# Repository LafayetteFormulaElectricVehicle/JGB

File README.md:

# LFEV 2015 CAN Communications Microprocessor #

## For now we have decided not to add JGBs to the system
JGBs provide good developement platforms but we will use the hardware and software in special configurations in each subsystem.

This directory contains the Lafayette College Formula Electric Vehicle CAN Communications Board. This board is responsible for relaying all low level inputs and outputs (ADC, D2A, GPIO) from vehicle sub-systems to the main SCADA computer. This design contains both hardware (PCB), and the firmware written for the device.

## Hardware ##
All hardware was created in KiCad (old-stable), and is located in the 'hardware' directory. The project is described in more detail there.

## Software ##
Software written for this project is located in the 'software' directory. The target architecture for the firmware is the ATMega16M1 AVR. Software build proceedures, programming the device, and project organization are all described in more detail in the folder.

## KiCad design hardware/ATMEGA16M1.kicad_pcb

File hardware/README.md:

# LFEV 2015 CAN Communications Microprocessor Hardware #
This directory contains the CAN communications board (JGB) designed for the spring 2015 semester.

## Overview ##
This circuit board is the primary interface between SCADA and all other systems. It is used to interface low level devices such as relays, ADCs, and other inputs/outputs to the SCADA computer via a CAN bus. This board was designed for prototyping purposes, and ensures consitant message format is used on the CAN bus. Any device which communicates via the CAN bus should inteface through this board.

The microcontroller present on this board, and the software which runs on it should eventually be integrated into each node which must communicate via the CAN bus.

## System Capabilities ##

## Target Device ##
This software is written for the **Atmel ATMEGA 16M1 Automotive AVR**  
  
This device was selected for its price, software availability, documentation and onboard CAN bus support.

1. [ATMega16M1 Overview](http://www.atmel.com/devices/atmega16m1.aspx)
2. [ATMega16M1 Datasheet](http://www.atmel.com/images/doc8209.pdf)

### Features ###

* Atmel® AVR® 8-bit microcontroller
* Up to 1 MIPS throughput per MHz
* 16KBytes flash of in-system programmable program memory
* 512B of in-system programmable EEPROM
* 1KBytes internal SRAM
* On-chip debug interface (debugWIRE)
* CAN 2.0A/B with six message objects - ISO 16845 certified
* Variable PWM duty cycle and frequency
* Synchronous update of all PWM registers
* Peripheral features
* One 8-bit general purpose timer/counter
* One 16-bit general purpose timer/counter
* One master/slave SPI serial interface
* 10-bit ADC
	* 11 single ended channels
	* Three differential ADC channel pairs (5×, 10×, 20×, 40×)
* 10-bit DAC for variable voltage reference (comparators, ADC)
* Programmable watchdog timer with separate on-chip oscillator
* On-chip temperature sensor

### Operating Specifications ###

- Operating voltage: 2.7V - 5.5V
- Extended operating temperature:
- -40°C to +85°C
- Core speed grade:
- 0 - 8MHz @ 2.7 - 4.5V
- 0 - 16MHz @ 4.5 - 5.5V

## EDA Software Suite ##

### EDA Software Suite: ###
KiCad 'old-stable' was used to design this PCB. The technical revision was KiCad (2013-may-18)-stable, run under Gentoo Linux. The source code can be found at [kicad-20130518.ebuild](https://packages.gentoo.org/package/sci-electronics/kicad)

### Component Libraries: ###
The following KiCad libraries were used in the creation of this PCB.

1. [Walter KiCad Libraries](http://smisioto.no-ip.org/elettronica/kicad/kicad-en.htm)

### Gerber Files ###
The latest GERBER files submitted for fabrication can be found in the repository under 'can-embd/hardware/gerber/' or in the BitBucket 'Downloads' page.

## Bill of Materials ##
All parts for this board were ordered through digikey, and have a DigiKey parts number (P/N) and URL associated with them in the KiCad schematic.  
  
These associations can also be viewed in the Bill of Materials (hardware/BOM.csv).  
A BOM (DigiKey ID: 2503580) has been created, which is summarized in the 'DigiKey BOM' file below. 

1. [DigiKey BOM](DigiKey_BOM.csv) This BOM contains the required DigiKey parts to build a single board.
2. [KiCad BOM](BOM.csv) This file contains a list of all components generated by KiCad.

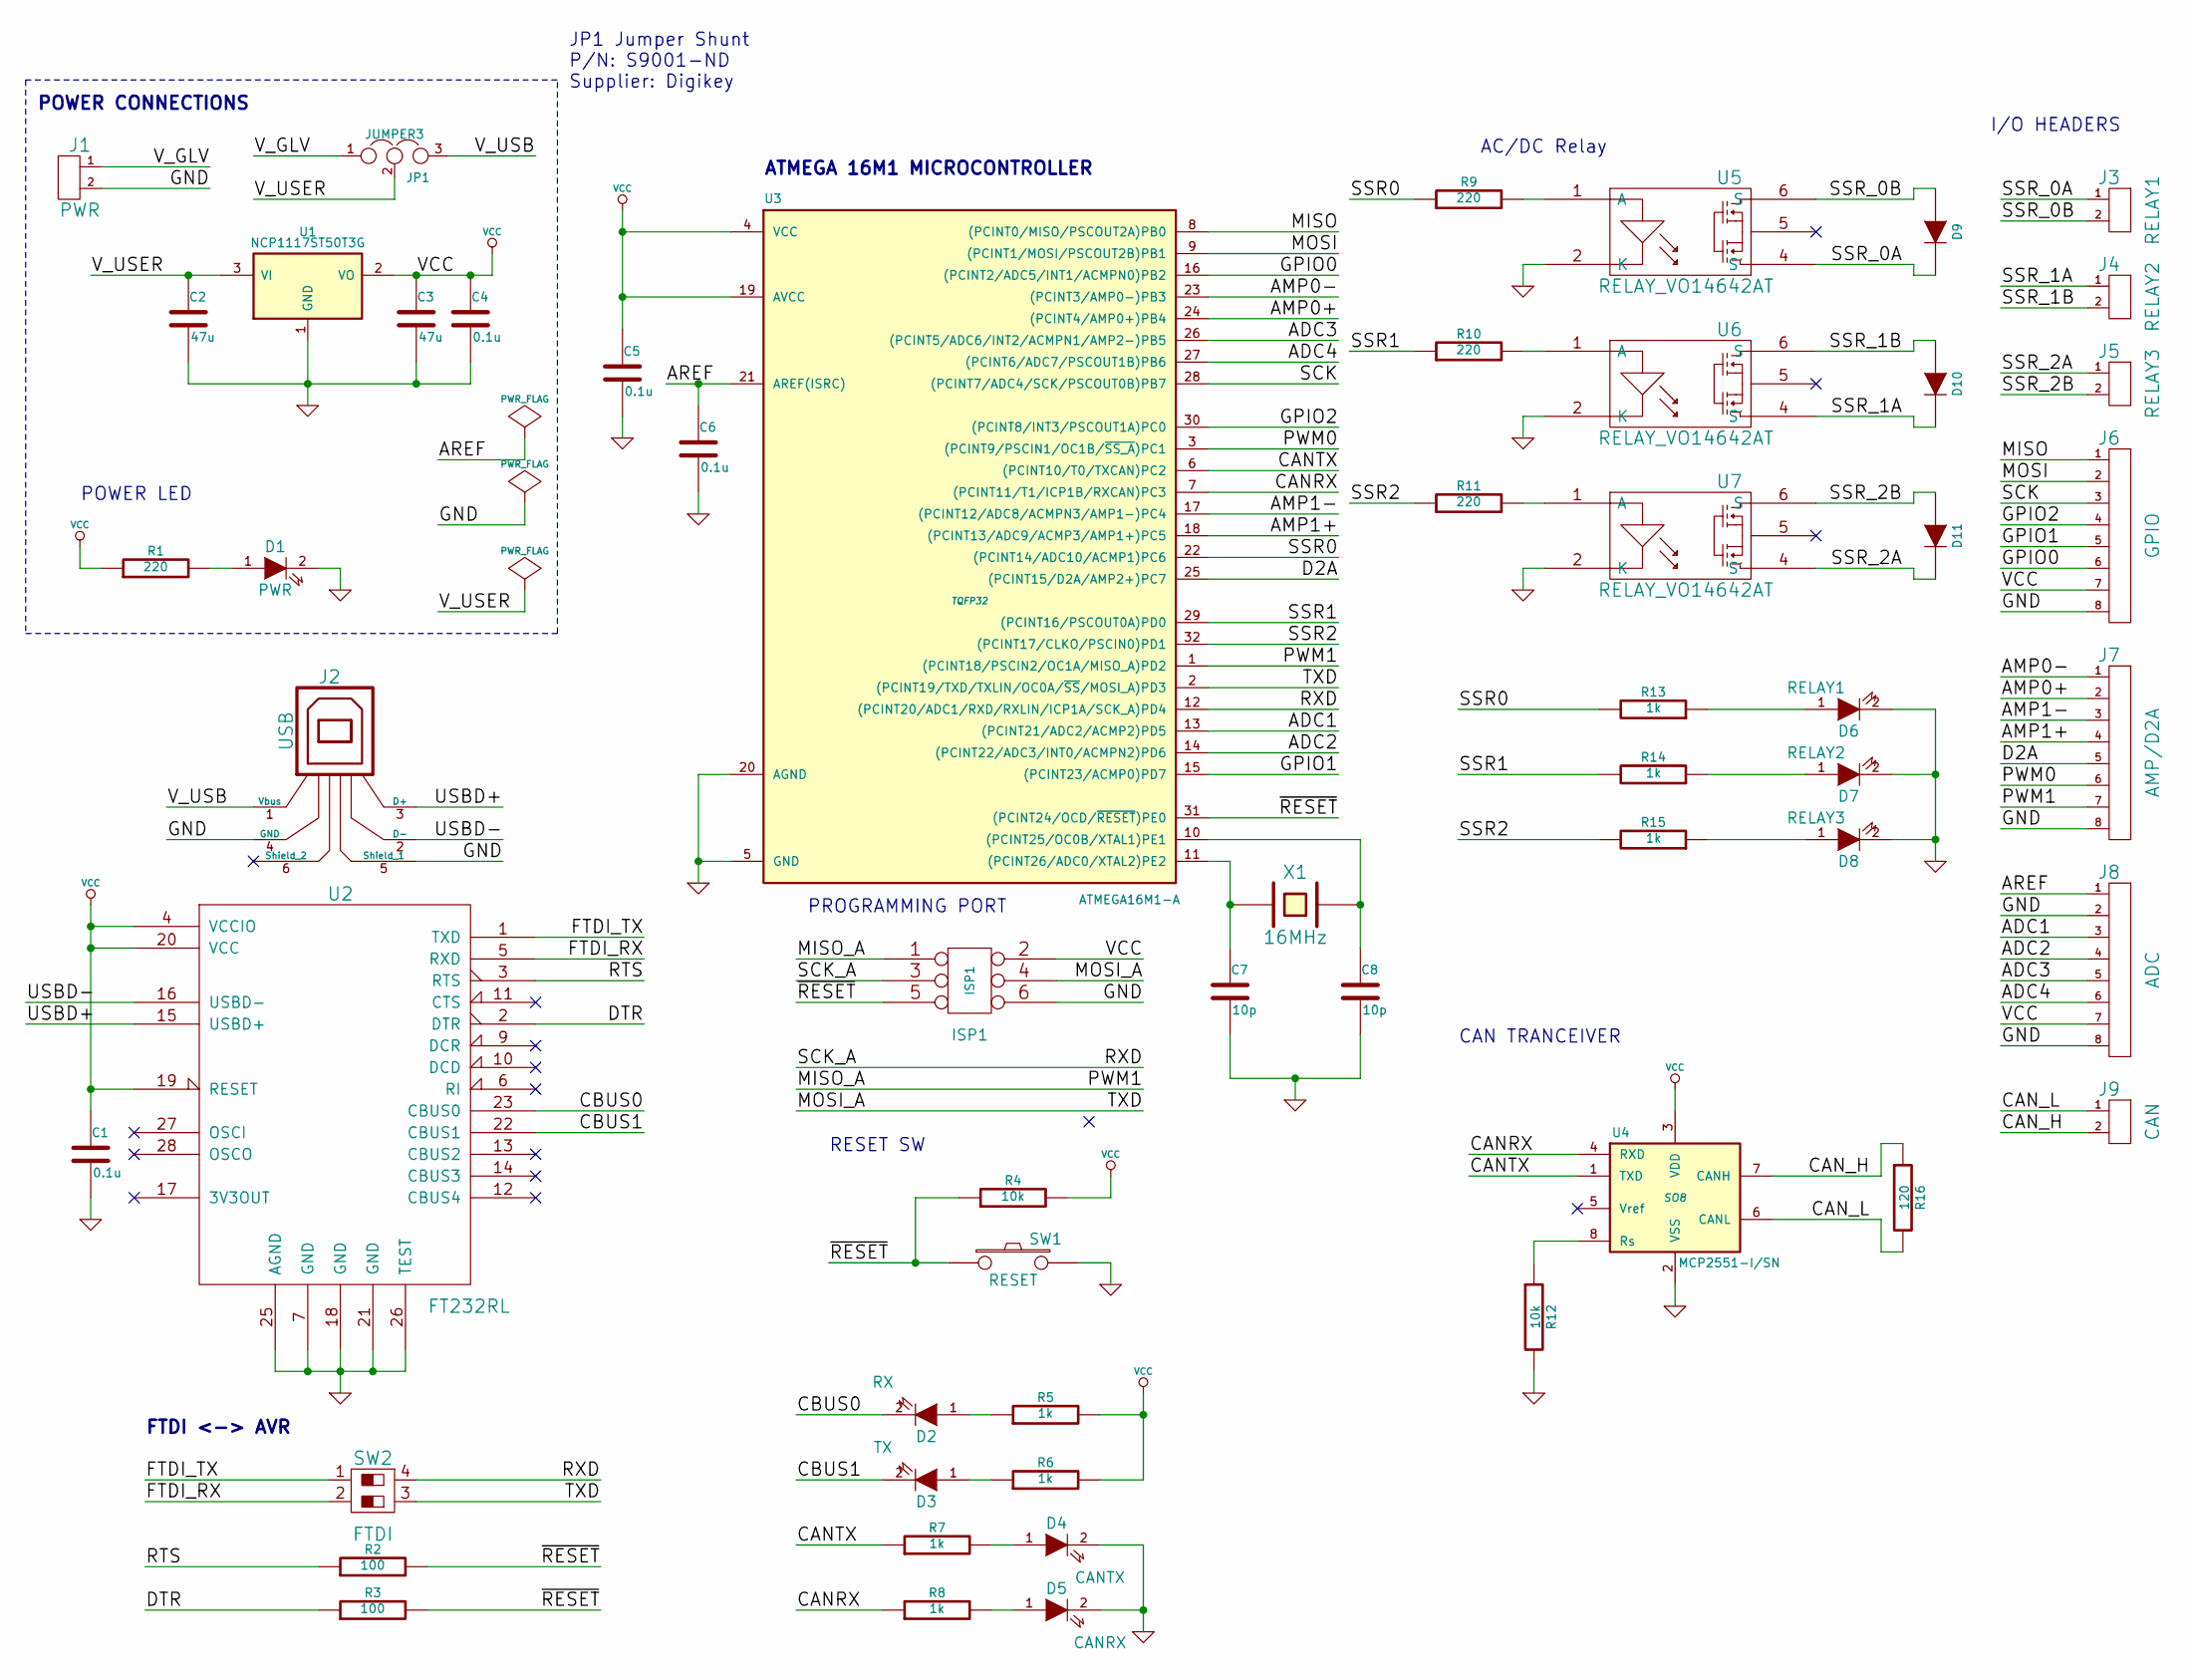
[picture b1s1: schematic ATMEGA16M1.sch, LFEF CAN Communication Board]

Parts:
C1, C4, C5, C6: 0.1u
C2, C3: 47u
C7, C8: 10p
D1: PWR
D2: RX
D3: TX
D4: CANTX
D5: CANRX
D6: RELAY1
D7: RELAY2
D8: RELAY3
D9, D10, D11: DIODE
ISP1: ISP1
J1: PWR
J2: USB
J3: RELAY1
J4: RELAY2
J5: RELAY3
J6: GPIO
J7: AMP/D2A
J8: ADC
J9: CAN
JP1: JUMPER3
R1, R9, R10, R11: 220
R2, R3: 100
R4, R12: 10k
R5, R6, R7, R8, R13, R14, R15: 1k
R16: 120
SW1: RESET
SW2: FTDI
U1: NCP1117ST50T3G
U2: FT232RL
U3: ATMEGA16M1-A; TQFP32
U4: MCP2551-I/SN; SO8
U5, U6, U7: RELAY_VO14642AT
X1: 16MHz

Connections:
/ADC1: J8.3, U3.13 ((PCINT21/ADC2/ACMP2)PD5)
/ADC2: J8.4, U3.14 ((PCINT22/ADC3/INT0/ACMPN2)PD6)
/ADC3: J8.5, U3.26 ((PCINT5/ADC6/INT2/ACMPN1/AMP2-)PB5)
/ADC4: J8.6, U3.27 ((PCINT6/ADC7/PSCOUT1B)PB6)
/AMP0+: J7.2, U3.24 ((PCINT4/AMP0+)PB4)
/AMP0-: J7.1, U3.23 ((PCINT3/AMP0-)PB3)
/AMP1+: J7.4, U3.18 ((PCINT13/ADC9/ACMP3/AMP1+)PC5)
/AMP1-: J7.3, U3.17 ((PCINT12/ADC8/ACMPN3/AMP1-)PC4)
/AREF: C6.1, J8.1, U3.21 (AREF(ISRC))
/CANRX: R8.1, U3.7 ((PCINT11/T1/ICP1B/RXCAN)PC3), U4.4 (RXD)
/CANTX: R7.1, U3.6 ((PCINT10/T0/TXCAN)PC2), U4.1 (TXD)
/CAN_H: J9.2, R16.1, U4.7 (CANH)
/CAN_L: J9.1, R16.2, U4.6 (CANL)
/CBUS0: D2.2 (K), U2.23 (CBUS0)
/CBUS1: D3.2 (K), U2.22 (CBUS1)
/D2A: J7.5, U3.25 ((PCINT15/D2A/AMP2+)PC7)
/DTR: R3.1, U2.2 (DTR)
/FTDI_RX: SW2.2, U2.5 (RXD)
/FTDI_TX: SW2.1, U2.1 (TXD)
/GPIO0: J6.6, U3.16 ((PCINT2/ADC5/INT1/ACMPN0)PB2)
/GPIO1: J6.5, U3.15 ((PCINT23/ACMP0)PD7)
/GPIO2: J6.4, U3.30 ((PCINT8/INT3/PSCOUT1A)PC0)
/MISO: J6.1, U3.8 ((PCINT0/MISO/PSCOUT2A)PB0)
/MISO_A: ISP1.1, J7.7, U3.1 ((PCINT18/PSCIN2/OC1A/MISO_A)PD2)
/MOSI: J6.2, U3.9 ((PCINT1/MOSI/PSCOUT2B)PB1)
/MOSI_A: ISP1.4, SW2.3, U3.2 ((PCINT19/TXD/TXLIN/OC0A/~SS~/MOSI_A)PD3)
/PWM0: J7.6, U3.3 ((PCINT9/PSCIN1/OC1B/~SS_A~)PC1)
/RTS: R2.1, U2.3 (RTS)
/RXD: ISP1.3, SW2.4, U3.12 ((PCINT20/ADC1/RXD/RXLIN/ICP1A/SCK_A)PD4)
/SCK: J6.3, U3.28 ((PCINT7/ADC4/SCK/PSCOUT0B)PB7)
/SSR0: R9.1, R13.2, U3.22 ((PCINT14/ADC10/ACMP1)PC6)
/SSR1: R10.1, R14.2, U3.29 ((PCINT16/PSCOUT0A)PD0)
/SSR2: R11.1, R15.2, U3.32 ((PCINT17/CLKO/PSCIN0)PD1)
/SSR_0A: D9.2 (K), J3.1, U5.4 (S')
/SSR_0B: D9.1 (A), J3.2, U5.6 (S)
/SSR_1A: D10.2 (K), J4.1, U6.4 (S')
/SSR_1B: D10.1 (A), J4.2, U6.6 (S)
/SSR_2A: D11.2 (K), J5.1, U7.4 (S')
/SSR_2B: D11.1 (A), J5.2, U7.6 (S)
/USBD+: J2.3 (D+), U2.15 (USBD+)
/USBD-: J2.2 (D-), U2.16 (USBD-)
/V_GLV: J1.1, JP1.1
/V_USB: J2.1 (Vbus), JP1.3
/V_USER: C2.1, JP1.2, U1.3 (VI)
/~RESET: ISP1.5, R2.2, R3.2, R4.1, SW1.1, U3.31 ((PCINT24/OCD/~RESET~)PE0)
GND: C1.2, C2.2, C3.2, C4.2, C5.2, C6.2, C7.2, C8.2, D1.2 (K), D4.2 (K), D5.2 (K), D6.2 (K), D7.2 (K), D8.2 (K), ISP1.6, J1.2, J2.4 (GND), J2.5 (Shield_1), J6.8, J7.8, J8.2, J8.8, R12.2, SW1.2, U1.1 (GND), U2.7 (GND), U2.18 (GND), U2.21 (GND), U2.25 (AGND), U2.26 (TEST), U3.5 (GND), U3.20 (AGND), U4.2 (VSS), U5.2 (K), U6.2 (K), U7.2 (K)
unnamed: R12.1, U4.8 (Rs)
unnamed: D7.1 (A), R14.1
unnamed: D3.1 (A), R6.1
unnamed: R11.2, U7.1 (A)
unnamed: R9.2, U5.1 (A)
unnamed: R10.2, U6.1 (A)
unnamed: D6.1 (A), R13.1
unnamed: D8.1 (A), R15.1
unnamed: D1.1 (A), R1.2
unnamed: D2.1 (A), R5.1
unnamed: D4.1 (A), R7.2
unnamed: D5.1 (A), R8.2
unnamed: C7.1, U3.11 ((PCINT26/ADC0/XTAL2)PE2), X1.1
unnamed: C8.1, U3.10 ((PCINT25/OC0B/XTAL1)PE1), X1.2
VCC: C1.1, C3.1, C4.1, C5.1, ISP1.2, J6.7, J8.7, R1.1, R4.2, R5.2, R6.2, U1.2 (VO), U2.4 (VCCIO), U2.19 (RESET), U2.20 (VCC), U3.4 (VCC), U3.19 (AVCC), U4.3 (VDD)

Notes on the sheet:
POWER CONNECTIONS
FTDI <-> AVR
ATMEGA 16M1 MICROCONTROLLER
AC/DC Relay
RESET SW
PROGRAMMING PORT
CAN TRANCEIVER
I/O HEADERS
POWER LED
JP1 Jumper Shunt P/N: S9001-ND Supplier: Digikey

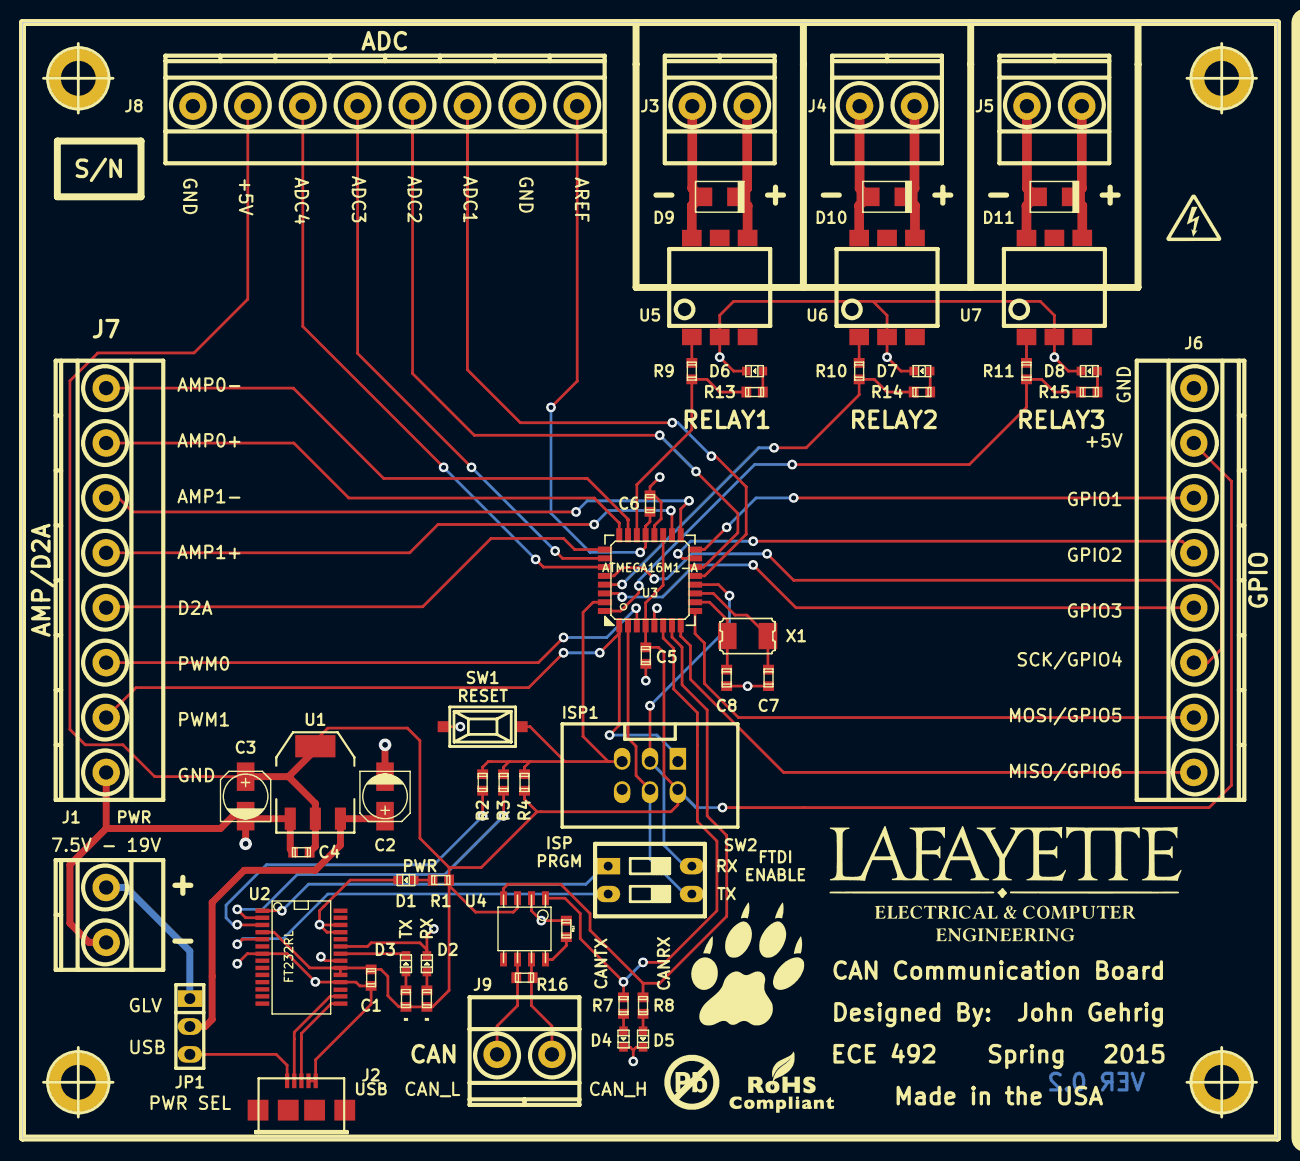
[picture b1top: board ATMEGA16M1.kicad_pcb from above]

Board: 2 copper layers, 114.3 x 101.6 mm, 60 parts (0 on the bottom side), 61 nets.

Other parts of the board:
hole_5mm, hole_5mm#2, hole_5mm#3, hole_5mm#4: VAL**; hole_5mm

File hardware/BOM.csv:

ref,value,datasheet,footprint,Field1,Field2,Field3,Field4,Field5,Field6,Field7,Field8
C1,0.1u,~,~,~,490-1524-1-ND,Digikey,http://www.digikey.com/product-detail/en/GRM188R71E104KA01D/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,,,,,
C2,47u,~,~,~,PCE5005CT-ND,Digikey,http://www.digikey.com/product-detail/en/EEE-FT1E470AR/PCE50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,,,,,
C3,47u,~,~,~,PCE5005CT-ND,Digikey,http://www.digikey.com/product-detail/en/EEE-FT1E470AR/PCE50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,,,,,
C4,0.1u,~,~,~,490-1524-1-ND,Digikey,http://www.digikey.com/product-detail/en/GRM188R71E104KA01D/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,,,,,
C5,0.1u,~,~,~,490-1524-1-ND,Digikey,http://www.digikey.com/product-detail/en/GRM188R71E104KA01D/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,,,,,
C6,0.1u,~,~,~,490-1524-1-ND,Digikey,http://www.digikey.com/product-detail/en/GRM188R71E104KA01D/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,,,,,
C7,10p,~,~,~,490-1403-1-ND,Digikey,http://www.digikey.com/product-detail/en/GRM1885C1H100JA01D/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,,,,,
C8,10p,~,~,~,490-1403-1-ND,Digikey,http://www.digikey.com/product-detail/en/GRM1885C1H100JA01D/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,,,,,
D1,PWR,~,~,~,732-4982-1-ND,Digikey,http://www.digikey.com/product-detail/en/150080BS75000/732-4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,,,,,
D2,RX,~,~,~,732-4981-1-ND,Digikey,http://www.digikey.com/product-detail/en/150060YS75000/732-4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,,,,,
D3,TX,~,~,~,732-4978-1-ND,Digikey,http://www.digikey.com/product-detail/en/150060RS75000/732-4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,,,,,
D4,CANTX,~,~,~,732-4978-1-ND,Digikey,http://www.digikey.com/product-detail/en/150060RS75000/732-4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,,,,,
D5,CANRX,~,~,~,732-4981-1-ND,Digikey,http://www.digikey.com/product-detail/en/150060YS75000/732-4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,,,,,
D6,RELAY1,~,~,~,732-4971-1-ND,Digikey,http://www.digikey.com/product-detail/en/150060GS75000/732-4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,,,,,
D7,RELAY2,~,~,~,732-4971-1-ND,Digikey,http://www.digikey.com/product-detail/en/150060GS75000/732-4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,,,,,
D8,RELAY3,~,~,~,732-4971-1-ND,Digikey,http://www.digikey.com/product-detail/en/150060GS75000/732-4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,,,,,
D9,DIODE,~,~,~,SK310A-LTPMSCT-ND,Digikey,http://www.digikey.com/product-detail/en/SK310A-LTP/SK310A-L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,,,,,
D10,DIODE,~,~,~,SK310A-LTPMSCT-ND,Digikey,http://www.digikey.com/product-detail/en/SK310A-LTP/SK310A-L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,,,,,
D11,DIODE,~,~,~,SK310A-LTPMSCT-ND,Digikey,http://www.digikey.com/product-detail/en/SK310A-LTP/SK310A-L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,,,,,
ISP1,ISP1,~,~,~,3M15451-ND,Digikey,http://www.digikey.com/product-detail/en/30306-6002HB/3M1545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,,,,,
J1,PWR,,,,ED2609-ND,Digikey,http://www.digikey.com/product-detail/en/OSTTC022162/ED2609-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,,,,,
J2,USB,,,,609-4613-1-ND,Digikey,http://www.digikey.com/product-detail/en/10118192-0001LF/609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,,,,,
J3,RELAY,,,,ED2609-ND,Digikey,http://www.digikey.com/product-detail/en/OSTTC022162/ED2609-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,,,,,
J4,RELAY,,,,ED2609-ND,Digikey,http://www.digikey.com/product-detail/en/OSTTC022162/ED2609-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,,,,,
J5,RELAY,,,,ED2609-ND,Digikey,http://www.digikey.com/product-detail/en/OSTTC022162/ED2609-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,,,,,
J6,GPIO,,,,ED2615-ND,Digikey,http://www.digikey.com/product-detail/en/OSTTC082162/ED2615-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,,,,,
J7,AMP/D2A,,,,ED2615-ND,Digikey,http://www.digikey.com/product-detail/en/OSTTC082162/ED2615-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,,,,,
J8,ADC,,,,ED2615-ND,Digikey,http://www.digikey.com/product-detail/en/OSTTC082162/ED2615-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,,,,,
J9,CAN,,,,ED2609-ND,Digikey,http://www.digikey.com/product-detail/en/OSTTC022162/ED2609-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,,,,,
JP1,JUMPER3,~,~,~,952-2264-ND,Digikey,http://www.digikey.com/product-detail/en/M20-9990346/952-226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,,,,,
R1,220,~,~,~,RHM220CGCT-ND,Digikey,http://www.digikey.com/product-detail/en/MCR03ERTJ221/RHM220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,,,,,
R2,100,~,~,~,,,,,,,,
R3,100,~,~,~,,,,,,,,
R4,10k,~,~,~,RHM10KCGCT-ND,Digikey,http://www.digikey.com/product-detail/en/MCR03ERTJ103/RHM10K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,,,,,
R5,1k,~,~,~,RHM1.0KCGCT-ND,Digikey,http://www.digikey.com/product-detail/en/MCR03ERTJ102/RHM1.0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,,,,,
R6,1k,~,~,~,RHM1.0KCGCT-ND,Digikey,http://www.digikey.com/product-detail/en/MCR03ERTJ102/RHM1.0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,,,,,
R7,1k,~,~,~,RHM1.0KCGCT-ND,Digikey,http://www.digikey.com/product-detail/en/MCR03ERTJ102/RHM1.0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,,,,,
R8,1k,~,~,~,RHM1.0KCGCT-ND,Digikey,http://www.digikey.com/product-detail/en/MCR03ERTJ102/RHM1.0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,,,,,
R9,220,~,~,~,RHM220CGCT-ND,Digikey,http://www.digikey.com/product-detail/en/MCR03ERTJ221/RHM220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,,,,,
R10,220,~,~,~,RHM220CGCT-ND,Digikey,http://www.digikey.com/product-detail/en/MCR03ERTJ221/RHM220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,,,,,
R11,220,~,~,~,RHM220CGCT-ND,Digikey,http://www.digikey.com/product-detail/en/MCR03ERTJ221/RHM220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,,,,,
R12,10k,~,~,~,RHM10KCGCT-ND,Digikey,http://www.digikey.com/product-detail/en/MCR03ERTJ103/RHM10K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,,,,,
R13,1k,~,~,~,RHM1.0KCGCT-ND,Digikey,http://www.digikey.com/product-detail/en/MCR03ERTJ102/RHM1.0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,,,,,
R14,1k,~,~,~,RHM1.0KCGCT-ND,Digikey,http://www.digikey.com/product-detail/en/MCR03ERTJ102/RHM1.0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,,,,,
R15,1k,~,~,~,RHM1.0KCGCT-ND,Digikey,http://www.digikey.com/product-detail/en/MCR03ERTJ102/RHM1.0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,,,,,
R16,120,~,~,~,,,,,,,,
SW1,RESET,~,~,~,401-1427-1-ND,Digikey,http://www.digikey.com/product-detail/en/KMR221GLFS/401-1427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,,,,,
SW2,FTDI,,,,,,,,,,,
U1,NCP1117ST50T3G,~,~,~,NCP1117ST50T3GOSCT-ND,Digikey,http://www.digikey.com/product-detail/en/NCP1117ST50T3G/NCP1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,,,,,
U2,FT232RL,~,~,~,768-1007-1-ND,Digikey,http://www.digikey.com/product-detail/en/FT232RL-REEL/768-10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,,,,,
U3,ATMEGA16M1-A,,TQFP32,,ATMEGA16M1-15AZCT-ND,Digikey,http://www.digikey.com/product-detail/en/ATMEGA16M1-15AZ/ATM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,,,,,
U4,MCP2551-I/SN,,SO8,,MCP2551T-E/SNCT-ND,Digikey,http://www.digikey.com/product-detail/en/MCP2551T-E%2FSN/MCP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,,,,,
U5,RELAY_VO14642AT,~,~,~,VO14642AABCT-ND,Digkey,http://www.digikey.com/product-detail/en/VO14642AABTR/VO1464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,,,,,
U6,RELAY_VO14642AT,~,~,~,VO14642AABCT-ND,Digikey,http://www.digikey.com/product-detail/en/VO14642AABTR/VO1464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,,,,,
U7,RELAY_VO14642AT,~,~,~,VO14642AABCT-ND,Digikey,http://www.digikey.com/product-detail/en/VO14642AABTR/VO1464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,,,,,
X1,16MHz,~,~,~,644-1037-1-ND,Digikey,http://www.digikey.com/product-detail/en/NX5032GA-16.000000M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,,,,,

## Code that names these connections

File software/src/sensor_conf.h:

#ifndef SENSOR_CONF_H
#define SENSOR_CONF_H

//GPIO
const  uint8_t GPIO0_BIT  = PB2;
const *uint8_t GPIO0_PIN  = PINB;
const *uint8_t GPIO0_PORT = PORTB;
const *uint8_t GPIO0_DDR  = DDRB;

const  uint8_t GPIO1_BIT  = PD7;
const *uint8_t GPIO1_PIN  = &PIND;
const *uint8_t GPIO1_PORT = &PORTD;
const *uint8_t GPIO1_DDR  = &DDRD;

const  uint8_t GPIO2_BIT  = PC0;
const *uint8_t GPIO2_PIN  = &PINC;
const *uint8_t GPIO2_PORT = &PORTC;
const *uint8_t GPIO2_DDR  = &DDRC;

const  uint8_t GPIO3_BIT  = PB7;
const *uint8_t GPIO3_PIN  = &PINB;
const *uint8_t GPIO3_PORT = &PORTB;
const *uint8_t GPIO3_DDR  = &DDRB;

const  uint8_t GPIO4_BIT  = PB1;
const *uint8_t GPIO4_PIN  = &PINB;
const *uint8_t GPIO4_PORT = &PORTB;
const *uint8_t GPIO4_DDR  = &DDRB;

const  uint8_t GPIO5_BIT  = PB0;
const *uint8_t GPIO5_PIN  = &PINB;
const *uint8_t GPIO5_PORT = &PORTB;
const *uint8_t GPIO5_DDR  = &DDRB;

struct in_config {
	uint8_t en : 1;
	uint8_t slot : 2;
	uint8_t frame: 3;
	uint16_t (*get_value)(void);
};

struct out_config {
	uint8_t en : 1;
	uint8_t slot : 2;
	uint8_t frame: 3;
	void (*set_value)(uint8_t);
};

struct bit_config {
	uint8_t en : 1;
	uint8_t ddr : 1;
	uint8_t bit : 4;
	uint8_t slot : 2;
	uint8_t frame: 3;
	*uint8_t pin;
	*uint8_t port;
	*uint8_t ddr;
	void (*set_value)(uint8_t);
	uint8_t (*get_value)(void);
};

struct sys_config {
	in_config adc_1;
	in_config adc_2;
	in_config adc_3;
	in_config adc_4;
	in_config amp_0;
	in_config amp_1;
	in_config amp_1;

	out_config d2a;
	out_config pwm_0;
	out_config pwm_1;
	out_config ssr_0;
	out_config ssr_1;
	out_config ssr_2;
	
	bit_config gpio0;
	bit_config gpio1;
	bit_config gpio2;
	bit_config gpio3;
	bit_config gpio4;
	bit_config gpio5;
};

//Setup pin directions, etc
void setup_io(struct *sys_config);


#endif

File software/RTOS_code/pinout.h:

#ifndef PINOUT_H
#define PINOUT_H

#define GPIO_INPUT          0b00
#define GPIO_INPUT_PULLUP   0b01
#define GPIO_OUTPUT_LOW     0b10
#define GPIO_OUTPUT_HIGH    0b11

/**
* @name 
* @{ */
#define HIGH  1
#define LOW   0
/**  @} */

/**
* @brief 
*/
typedef struct {
	void* prt_reg,
	void* ddr_reg,
	void* pin_reg,
	uint8_t pin_num,
} GPIO_PIN;


/**
* @name 
* @{ */
// PORTA gpio pins
static const GPIO_PIN WATCHDOG    =  {&PORTA, &DDRA, &PINA, 0};
static const GPIO_PIN SW_SDA      =  {&PORTA, &DDRA, &PINA, 1};
static const GPIO_PIN SW_SCL      =  {&PORTA, &DDRA, &PINA, 2};
static const GPIO_PIN SLOOP_CTRL  =  {&PORTA, &DDRA, &PINA, 3};
static const GPIO_PIN CHRG_CTRL   =  {&PORTA, &DDRA, &PINA, 4};
static const GPIO_PIN FAN_CTRL    =  {&PORTA, &DDRA, &PINA, 5};

// PORTB gpio pins
static const GPIO_PIN GPIO_PB0    =  {&PORTB, &DDRB, &PINB, 0};
static const GPIO_PIN GPIO_PB1    =  {&PORTB, &DDRB, &PINB, 1};
static const GPIO_PIN GPIO_PB2    =  {&PORTB, &DDRB, &PINB, 2};
static const GPIO_PIN GPIO_PB3    =  {&PORTB, &DDRB, &PINB, 3};
static const GPIO_PIN GPIO_PB4    =  {&PORTB, &DDRB, &PINB, 4};
static const GPIO_PIN GPIO_PB5    =  {&PORTB, &DDRB, &PINB, 5};
static const GPIO_PIN GPIO_PB6    =  {&PORTB, &DDRB, &PINB, 6};
static const GPIO_PIN GPIO_PB7    =  {&PORTB, &DDRB, &PINB, 7};

// PORTC gpio pins
static const GPIO_PIN FAULT       =  {&PORTC, &DDRC, &PINC, 0};
static const GPIO_PIN REQUEST     =  {&PORTC, &DDRC, &PINC, 1};
static const GPIO_PIN LOW_VOLT    =  {&PORTC, &DDRC, &PINC, 2};

// PORTF gpio pins
static const GPIO_PIN GPIO_ADC0   =  {&PORTF, &DDRF, &PINF, 0};
static const GPIO_PIN GPIO_ADC1   =  {&PORTF, &DDRF, &PINF, 1};
static const GPIO_PIN GPIO_ADC2   =  {&PORTF, &DDRF, &PINF, 2};
static const GPIO_PIN GPIO_ADC3   =  {&PORTF, &DDRF, &PINF, 3};
/**  @} */


/**
* @brief 
*
* @param pin
* @param mode
*/
static inline void pinMode(GPIO_PIN pin, uint8_t mode) {
	*(pin.ddr_reg) = 
}


/**
* @brief 
*
* @param pin
* @param value
*/
static inline void pinWrite(GPIO_PIN pin, uint8_t value) {
	pin.
	*PORT = (*PORT & _BV(pin)) | (value << pin);
}


/**
* @brief 
*
* @param pin
*
* @return 
*/
static inline uint8_t pinRead(GPIO_PIN pin) {
	
}


#endif /*PINOUT_H*/

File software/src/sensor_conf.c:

#include "sensor_conf.h"

#include <avr/eeprom.h>

void setup_io(struct sys_config *sys) {
	DDRA = 0; 
	DDRB = 0;
	DDRC = 0;
	DDRD = 0;
	
	//ADC1
	sys->adc_1->en = 0;
	sys->adc_1->ddr = 0;
	sys->adc_1->slot = 0;
	sys->adc_1->frame = 0;
	sys->adc_1->get_value = 0;
	
	
	//ADC2
	sys->adc_2->en = 0;
	sys->adc_2->ddr = 0;
	sys->adc_2->slot = 0;
	sys->adc_2->frame = 0;
	sys->adc_1->get_value = 0;
	
	//ADC3
	sys->adc_3->en = 0;
	sys->adc_3->ddr = 0;
	sys->adc_3->slot = 0;
	sys->adc_3->frame = 0;
	sys->adc_1->get_value = 0;
	
	//ADC4
	sys->adc_4;
	sys->adc_4->en = 0;
	sys->adc_4->ddr = 0;
	sys->adc_4->slot = 0;
	sys->adc_4->frame = 0;
	sys->adc_1->get_value = 0;
	
	//AMP0
	sys->amp_0->en = 0;
	sys->amp_0->ddr = 0;
	sys->amp_0->slot = 0;
	sys->amp_0->frame = 0;
	
	//AMP1
	sys->amp_1->en = 0;
	sys->amp_1->ddr = 0;
	sys->amp_1->slot = 0;
	sys->amp_1->frame = 0;
	
	//D2A
	sys->d2a;
	sys->d2a->en = 0;
	sys->d2a->ddr = 0;
	sys->d2a->slot = 0;
	sys->d2a->frame = 0;
	DDRC |= (1 << PC7);
	
	//PWM0
	sys->pwm_0->en = 0;
	sys->pwm_0->ddr = 0;
	sys->pwm_0->slot = 0;
	sys->pwm_0->frame = 0;
	DDRC |= (1 << PC1);
	
	//PWM1
	sys->pwm_1->en = 0;
	sys->pwm_1->ddr = 0;
	sys->pwm_1->slot = 0;
	sys->pwm_1->frame = 0;
	DDRD |= (1 << PD2);
	
	//SSR0
	sys->ssr_0->en = 0;
	sys->ssr_0->ddr = 0;
	sys->ssr_0->slot = 0;
	sys->ssr_0->frame = 0;
	DDRC |= (1 << PC6);
	
	//SSR1
	sys->ssr_1->en = 0;
	sys->ssr_1->ddr = 0;
	sys->ssr_1->slot = 0;
	sys->ssr_1->frame = 0;
	DDRC |= (1 << PD0);
	
	//SSR2
	sys->ssr_2->en = 0;
	sys->ssr_2->ddr = 0;
	sys->ssr_2->slot = 0;
	sys->ssr_2->frame = 0;
	DDRC |= (1 << PD1);
}

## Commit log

2017-01-27 Pushed up John's old work
2017-01-28 Pushed up old software that was worked on in 2016
2017-01-28 Started to create jgb file. Documentating ADC and D2A functions
2017-01-29 Worked on testing DAC
2017-01-29 Updated main to test functions in a more tidy method
2017-01-29 Started to add analog comparator
2017-01-29 added relay functionality
2017-01-29 Worked on getting ac working
2017-01-29 Added GPIO Functionality
2017-01-29 Added documentation to GPIO functionality in jgb.h
2017-01-29 added GPIO pull up resistor activation
2017-01-29 Removed analog compare. Need to implement differential amplifier
2017-01-29 Merged ADC.h into JGB.h
2017-01-29 cleaned up some of the files to be error-free in avr design ide
2017-01-30 Added code that can allow us to develop code on a RTOS
2017-02-02 added can_bust_test.c
2017-02-02 updated can_bus_test.c (isn't quite working yet) :(
2017-02-03 Updated schematic for JGB
2017-02-21 added can_test_board.c for jgb can test board
2017-04-06 New Project Added
2017-04-07 Fixes to UART library.
2017-04-10 Changes to fix uart
2017-04-19 CAN Sending + Receiving
2017-05-03 Changes towards PWm
2017-05-03 Changes to final demo
